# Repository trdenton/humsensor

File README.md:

# Humidity Sensor Solution

A basic wireless humidity sensor solution.  A work in progress.  Get your PCBs at https://www.pcbway.com/project/shareproject/W04152ASD12_humxmit_v2.html

Check out the writeup here:
https://skullspace.ca/2017/12/23/wireless-humidity-sensor-part-1-hardware-design/

## Hardware

Check out the KiCAD design files for the transmitter/sensor in 'tx\_pcb'

## Software

### Receiver

The receiver is based on an arduino mega (due to what I had laying around) and an nRF24L01+ module.  The sketch can be fond in 'hum\_sw/humrx'

### Transmitter

The transmitter is based on an attiny87, si7006, and nrf24L01+.  You can find it's source code in 'hum\_sw/humtx'.  It requires avrlibc and GNU make.  the 'prog' subdirectory contains a scrip that will flash the transmitter PCB via avrdude.  The included copy of avrdude is for my convenience, it is compiled for linux amd64

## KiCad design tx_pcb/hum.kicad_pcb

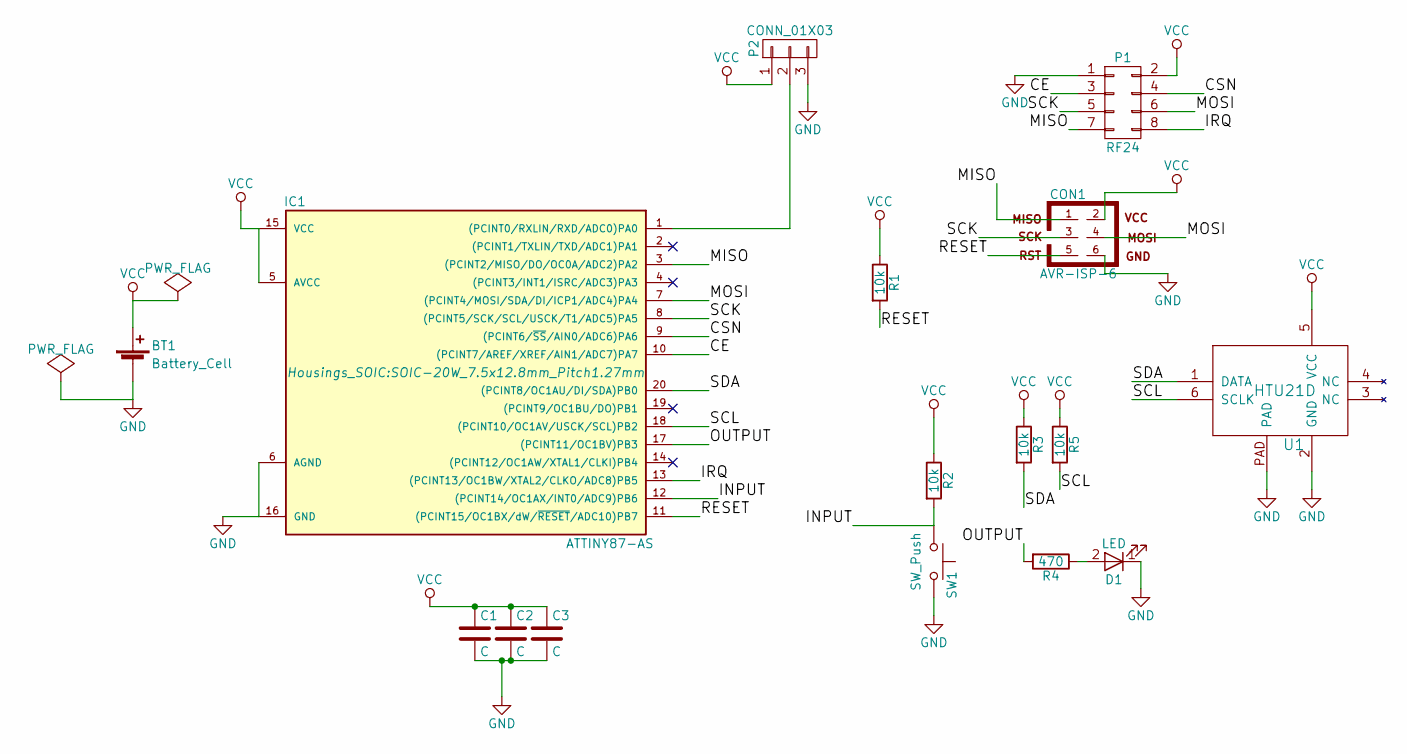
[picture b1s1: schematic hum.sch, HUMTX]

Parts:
BT1: Battery_Cell; battery
C1, C2, C3: C; C_0402
CON1: AVR-ISP-6; Pin_Header_Straight_2x03
D1: LED; LED_1206
IC1: ATTINY87-AS; SOIC-20W_7.5x12.8mm_Pitch1.27mm
P1: RF24; Socket_Strip_Straight_2x04
P2: CONN_01X03; Socket_Strip_Straight_1x03
R1, R2, R3, R5: 10k; R_0402
R4: 470; R_0402
SW1: SW_Push; switch
U1: HTU21D

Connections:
/CE: IC1.10 ((PCINT7/AREF/XREF/AIN1/ADC7)PA7), P1.3
/CSN: IC1.9 ((PCINT6/~SS~/AIN0/ADC6)PA6), P1.4
/INPUT: IC1.12 ((PCINT14/OC1AX/INT0/ADC9)PB6), R2.2, SW1.1
/IRQ: IC1.13 ((PCINT13/OC1BW/XTAL2/CLKO/ADC8)PB5), P1.8
/MISO: CON1.1, IC1.3 ((PCINT2/MISO/DO/OC0A/ADC2)PA2), P1.7
/MOSI: CON1.4, IC1.7 ((PCINT4/MOSI/SDA/DI/ICP1/ADC4)PA4), P1.6
/OUTPUT: IC1.17 ((PCINT11/OC1BV)PB3), R4.2
/RESET: CON1.5, IC1.11 ((PCINT15/OC1BX/dW/~RESET~/ADC10)PB7), R1.2
/SCK: CON1.3, IC1.8 ((PCINT5/SCK/SCL/USCK/T1/ADC5)PA5), P1.5
/SCL: IC1.18 ((PCINT10/OC1AV/USCK/SCL)PB2), R5.2, U1.6 (SCLK)
/SDA: IC1.20 ((PCINT8/OC1AU/DI/SDA)PB0), R3.2, U1.1 (DATA)
GND: BT1.2 (-), C1.2, C2.2, C3.2, CON1.6, D1.1 (K), IC1.6 (AGND), IC1.16 (GND), P1.1, P2.3, SW1.2, U1.2 (GND), U1.PAD
unnamed: D1.2 (A), R4.1
unnamed: IC1.1 ((PCINT0/RXLIN/RXD/ADC0)PA0), P2.2
VCC: BT1.1 (+), C1.1, C2.1, C3.1, CON1.2, IC1.5 (AVCC), IC1.15 (VCC), P1.2, P2.1, R1.1, R2.1, R3.1, R5.1, U1.5 (VCC)

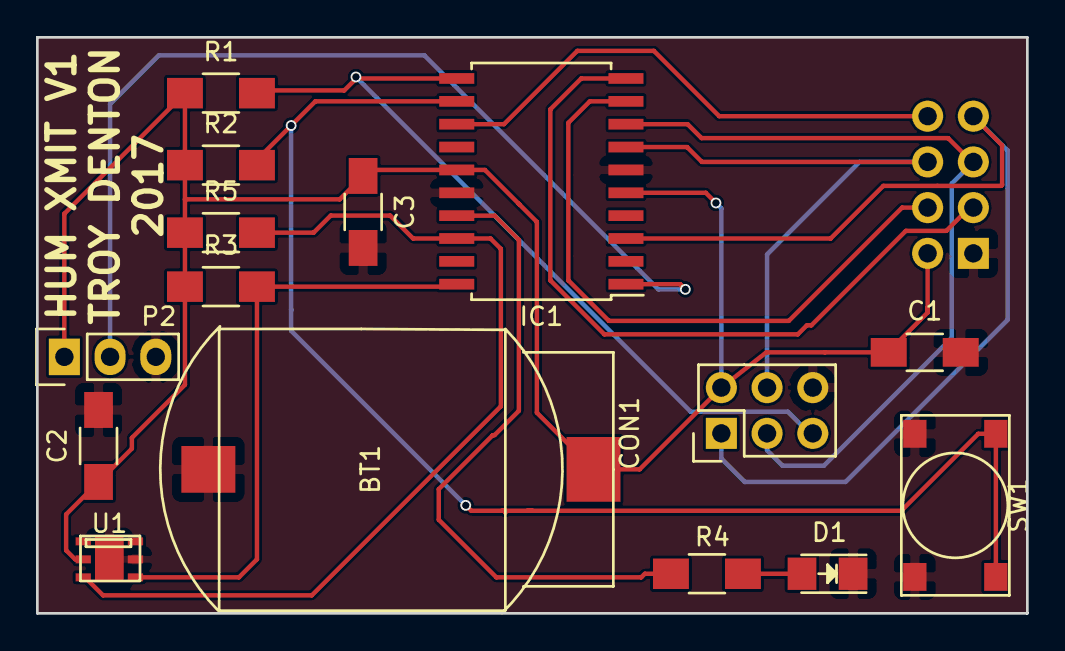
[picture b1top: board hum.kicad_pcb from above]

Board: 2 copper layers, 55.0 x 32.0 mm, 16 parts (1 on the bottom side), 15 nets.

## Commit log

2017-12-23 added all projects into one repo
2017-12-23 Add README.md'
2017-12-23 add link to PCBs
2018-01-26 now using float for humidity payload on transmitter
2018-01-26 reduced transmission rate - I think I bricked one of my transmitters with the previous config
